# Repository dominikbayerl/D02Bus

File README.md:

# D02Bus

D0-2-Bus ("D0 to Bus") is an Open Hardware project designed to convert data from an energy smart meter D0 optical interface to RS485 Modbus.

## Overview

 This project aims to be compatible with various commercial smart meters (such as Eastron SDM, Kostal EnergyMeter, etc.), enabling easy integration into Modbus-based energy management systems.

## Inspiration & Attribution

This project is inspired by (and is essentially a "shameless copy" of) the "Smartmeter" project by **Niklas Menke**.
*   Original Project: [https://www.niklas-menke.de/projekte/smartmeter-auslesen/modbus/](https://www.niklas-menke.de/projekte/smartmeter-auslesen/modbus/)

## Key Differences

While based on the original concept, D02Bus implements specific changes for better usability:

*   **Microcontroller**: The hardware uses a **CH552G** microcontroller instead of the original ATtiny. This change provides better component availability and features a built-in USB controller for easier configuration.
*   **Firmware Flexibility**: The firmware aims to be more easily adjustable to support different smart meter models.

## Project Status

**⚠️ Warning: Work in Progress**

Currently, this project only contains **unvalidated** hardware designs. The repository will be updated once the first PCBs have been assembled and tested.

## License

This project is licensed under the **Creative Commons Attribution-NonCommercial-ShareAlike 4.0 International (CC BY-NC-SA 4.0)** license.

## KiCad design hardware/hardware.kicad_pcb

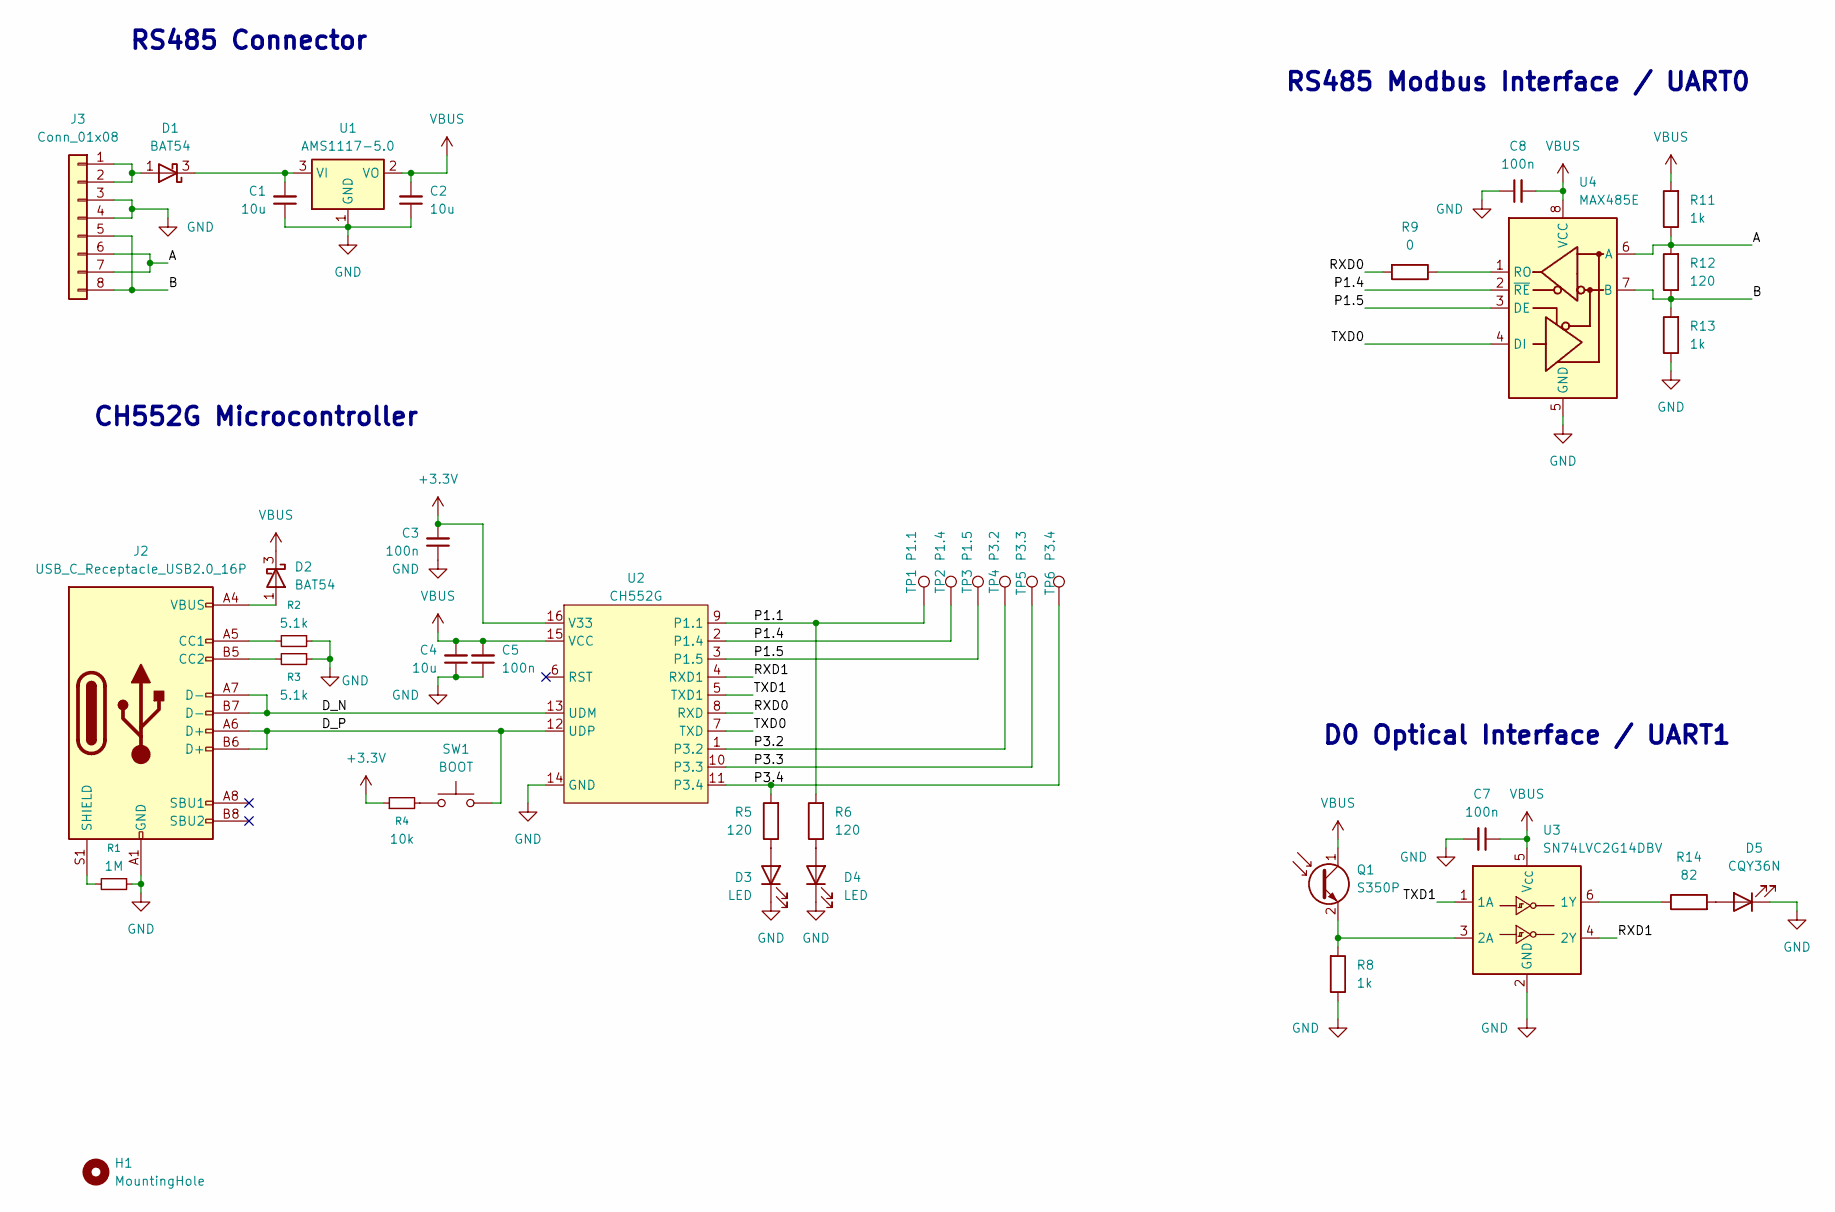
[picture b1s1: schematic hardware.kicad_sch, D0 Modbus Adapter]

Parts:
C1, C2, C4: 10u; C_0805_2012Metric_Pad1.18x1.45mm_HandSolder
C3, C5, C7, C8: 100n; C_0805_2012Metric_Pad1.18x1.45mm_HandSolder
D1, D2: BAT54; SOT-23
D3, D4: LED; LED_0805_2012Metric
D5: CQY36N; LED_D1.8mm_W3.3mm_H2.4mm
H1: MountingHole; MountingHole_3.2mm_M3_DIN965
J2: USB_C_Receptacle_USB2.0_16P; USB_C_Receptacle_HRO_TYPE-C-31-M-12
J3: Conn_01x08; TerminalBlock_Xinya_XY308-2.54-8P_1x08_P2.54mm_Horizontal
Q1: S350P; LED_D1.8mm_W3.3mm_H2.4mm
R1: 1M; R_0805_2012Metric_Pad1.20x1.40mm_HandSolder
R2, R3: 5.1k; R_0805_2012Metric_Pad1.20x1.40mm_HandSolder
R4: 10k; R_0805_2012Metric_Pad1.20x1.40mm_HandSolder
R5, R6, R12: 120; R_0805_2012Metric_Pad1.20x1.40mm_HandSolder
R8, R11, R13: 1k; R_0805_2012Metric_Pad1.20x1.40mm_HandSolder
R9: 0; R_0805_2012Metric_Pad1.20x1.40mm_HandSolder
R14: 82; R_0805_2012Metric_Pad1.20x1.40mm_HandSolder
SW1: BOOT; SW_SPST_4x3x2
TP1: P1.1; TestPoint_Pad_D1.0mm
TP2: P1.4; TestPoint_Pad_D1.0mm
TP3: P1.5; TestPoint_Pad_D1.0mm
TP4: P3.2; TestPoint_Pad_D1.0mm
TP5: P3.3; TestPoint_Pad_D1.0mm
TP6: P3.4; TestPoint_Pad_D1.0mm
U1: AMS1117-5.0; SOT-223-3_TabPin2
U2: CH552G; SOIC-16_3.9x9.9mm_P1.27mm
U3: SN74LVC2G14DBV; SOT-23-6
U4: MAX485E; SOIC-8_3.9x4.9mm_P1.27mm

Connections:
+3.3V: C3.2, R4.1, U2.16 (V33)
/A: J3.6, J3.7, R11.1, R12.2, U4.6 (A)
/B: J3.5, J3.8, R12.1, R13.2, U4.7 (B)
/D_N: J2.A7 (D-), J2.B7 (D-), U2.13 (UDM)
/D_P: J2.A6 (D+), J2.B6 (D+), SW1.2, U2.12 (UDP)
/P1.1: R6.2, TP1.1, U2.9 (P1.1)
/P1.4: TP2.1, U2.2 (P1.4), U4.2 (~RE)
/P1.5: TP3.1, U2.3 (P1.5), U4.3 (DE)
/P3.2: TP4.1, U2.1 (P3.2)
/P3.3: TP5.1, U2.10 (P3.3)
/P3.4: R5.2, TP6.1, U2.11 (P3.4)
/RXD0: R9.2, U2.8 (RXD)
/RXD1: U2.4 (RXD1), U3.4 (2Y)
/TXD0: U2.7 (TXD), U4.4 (DI)
/TXD1: U2.5 (TXD1), U3.1 (1A)
GND: C1.1, C2.1, C3.1, C4.1, C5.1, C7.2, C8.1, D3.1 (K), D4.1 (K), D5.1 (K), J2.A1 (GND), J2.A12 (GND), J2.B1 (GND), J2.B12 (GND), J3.3, J3.4, R1.1, R2.1, R3.1, R8.1, R13.1, U1.1 (GND), U2.14 (GND), U3.2 (GND), U4.5 (GND)
unnamed: D1.1 (A), J3.1, J3.2
unnamed: C1.2, D1.3 (K), U1.3 (VI)
unnamed: D2.1 (A), J2.A4 (VBUS), J2.A9 (VBUS), J2.B4 (VBUS), J2.B9 (VBUS)
unnamed: D3.2 (A), R5.1
unnamed: D4.2 (A), R6.1
unnamed: D5.2 (A), R14.2
unnamed: J2.A5 (CC1), R2.2
unnamed: J2.B5 (CC2), R3.2
unnamed: J2.S1 (SHIELD), R1.2
unnamed: Q1.2 (E), R8.2, U3.3 (2A)
unnamed: R4.2, SW1.1
unnamed: R14.1, U3.6 (1Y)
unnamed: R9.1, U4.1 (RO)
VBUS: C2.2, C4.2, C5.2, C7.1, C8.2, D2.3 (K), Q1.1 (C), R11.2, U1.2 (VO), U2.15 (VCC), U3.5 (V_{CC}), U4.8 (VCC)

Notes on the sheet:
RS485 Connector
D0 Optical Interface / UART1
RS485 Modbus Interface / UART0
CH552G Microcontroller

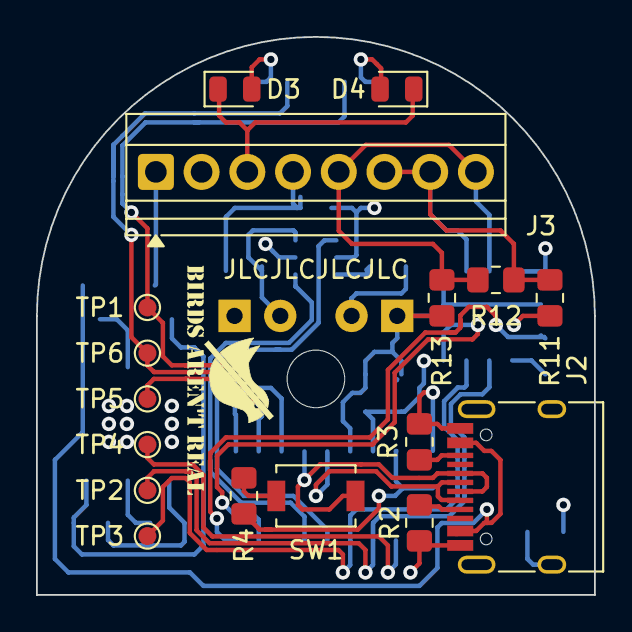
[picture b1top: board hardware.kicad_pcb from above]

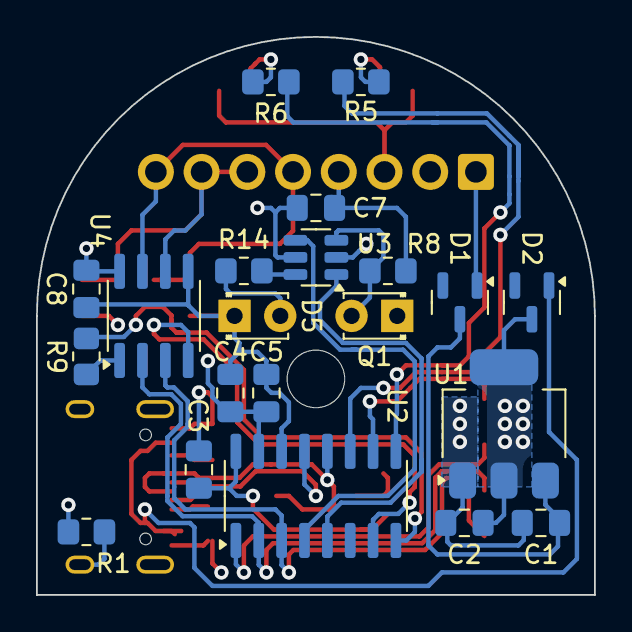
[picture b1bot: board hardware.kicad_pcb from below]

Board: 4 copper layers, 31.0 x 31.0 mm, 39 parts (21 on the bottom side), 30 nets.

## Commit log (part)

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2026-01-28 Import KiCad project.
2026-01-28 Add GitHub housekeeping information.
2026-03-31 Add WIP firmware.
2026-04-05 Update firmware. Modbus is pretty much working at this point.
2026-04-08 Add (untested) SML implementation.
2026-04-19 Fix test_modbus.c includes Unity is already on the include path.
2026-04-19 Improve SML parser. The original plan was to get away with a finite state machine (FSM) for parsing the SML protocol for minimum ressource consumption. However, the SML protocol is a Type-I grammar. 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
    The implementation is astonishingly efficient.
2026-04-19 Add vm_debug.c test tool. This tool provides a debugging harness for the SML vm.
2026-04-20 Add SML parser unit tests.
2026-04-27 Add OBIS parsing.
